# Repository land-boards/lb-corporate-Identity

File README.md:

corporate-Identity
==================

This is where we keep our corporate identity stuff like logos, mission statements, etc.

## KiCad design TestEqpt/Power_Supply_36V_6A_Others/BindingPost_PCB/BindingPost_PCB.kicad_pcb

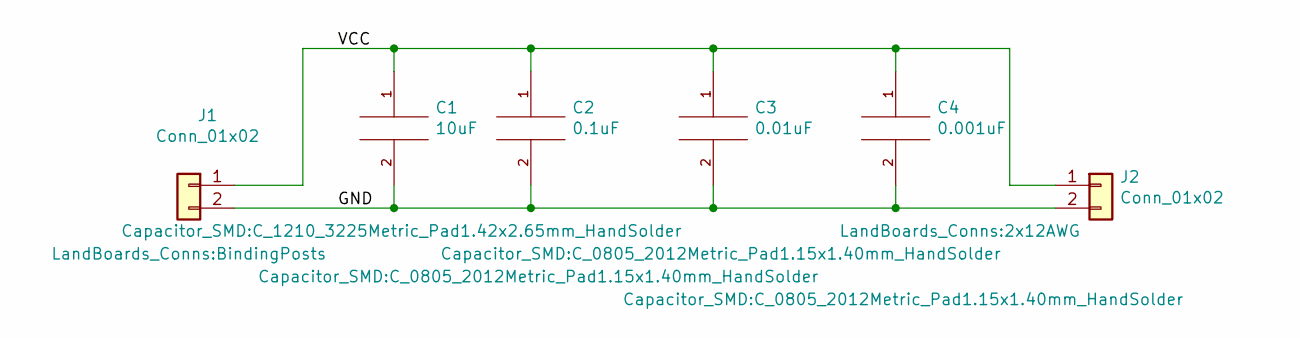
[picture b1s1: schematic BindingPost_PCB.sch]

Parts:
C1: 10uF; C_1210_3225Metric_Pad1.42x2.65mm_HandSolder
C2: 0.1uF; C_0805_2012Metric_Pad1.15x1.40mm_HandSolder
C3: 0.01uF; C_0805_2012Metric_Pad1.15x1.40mm_HandSolder
C4: 0.001uF; C_0805_2012Metric_Pad1.15x1.40mm_HandSolder
J1: Conn_01x02; BindingPosts
J2: Conn_01x02; 2x12AWG

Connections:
/GND: C1.2, C2.2, C3.2, C4.2, J1.2, J2.2
/VCC: C1.1, C2.1, C3.1, C4.1, J1.1, J2.1

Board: 2 copper layers, 6 parts (0 on the bottom side), 2 nets, no tracks yet.

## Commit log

2014-05-19 Created logos
2014-05-19 Added 140 pixel wide optimized as github icon
2014-05-19 Updated README to better describe what goes in this folder.
2014-06-09 Different sized logos
2014-07-18 thumbs?
2014-08-02 added facility and logos
2014-08-06 stuff
2014-08-07 web updTE
2014-08-09 more stuff
2014-08-12 latest
2014-08-12 updated paypal table
    updated paypal table
2014-08-12 working stores
2014-08-14 thumbs
2014-08-18 pics
2014-08-18 Created 640x480 image for video endings
2014-08-23 updated tinygrid85 page
2014-08-23 Saved SOW template
2014-09-02 Kicad logo
2014-09-19 Raspi-Plus-GVS-Cfg Web
2014-10-20 More tindies
2014-10-21 more logos
2014-10-23 Chinese national holiday statistics
2014-10-24 added ignore
2014-10-27 ignore
2014-10-30 China National Holiday
2014-11-20 rpi-mdi redirect
2014-12-04 Shipping charges for 10cm square cards
2014-12-14 card tables
2014-12-15 China shipment via USPS
2014-12-31 logos
2015-01-13 logo
2015-02-03 facilities
2015-02-13 added web content
2015-03-06 RPP-UIO-16
2015-03-31 tg85
2015-05-18 RPI-Console webpage
2015-06-18 schematic
2015-06-23 ignores added
2015-07-04 badges
2015-07-18 ognores
2015-08-13 Maker Faire
2015-08-28 DIGIO-128 webpage
2015-08-28 sticker for Screwduino
2015-09-30 MF2015 Stuff
2015-10-03 QR codes page
2015-11-01 MakerFaire
2015-11-12 banner
2015-12-22 more web shortcuts
2016-02-27 pics of the facility
2016-05-30 webpage for RPPSOC
2016-07-11 wide aspect ratio logo
2016-07-23 rpi consule page
2016-10-25 PiCluster redirect
2017-01-17 Added redirects
2017-01-31 Pgh logos
2017-02-06 Worked Social Media
2017-02-20 facility pics
2017-02-28 Made 320px verion
2017-09-05 Cable hanger rack
2018-07-28 Chinese New Year
2018-08-10 workmanship and cleanliness standards
2020-01-01 Webpage stuff
2020-01-02 web stuff
2020-01-05 web links
2020-01-31 web content
2020-02-20 Schematics for web
2020-02-24 schematics
2020-06-25 test eqt
2020-06-28 MILLIOHM METER
2020-08-03 More test eqpt
2021-02-06 rf test kit
2021-05-13 web and labels
2021-07-21 Test Eqpt
2021-07-22 Octopus Tester
2021-07-23 Meter
2021-08-05 Bind Post PCB
2021-08-16 HP AC voltmeter
2021-10-28 RF test card
2022-03-17 designs
2022-03-29 Move around icons
2022-03-30 more corp identity
2022-04-09 Add web docs
2022-05-23 Arduino in a Box
2022-06-19 Card pages
2022-06-19 I2CIO16-DB25 card links
2022-07-29 sensor card
2022-08-01 PicoVGA01
2022-08-20 HP 3200B
2022-08-27 HP 3200B and web stuff
2022-11-25 NEW CARDS
2022-11-28 web pages for new cards
2022-12-01 IBOMs
2022-12-06 Card web pages
2023-02-02 ER-MOZZI-DB
2024-06-27 More web stuff
2024-09-20 HTML UPDATES
